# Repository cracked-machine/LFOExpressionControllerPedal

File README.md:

# LFOExpressionControllerPedal
This pedal replaces the traditional treadle/rocker expression pedal as an input into other guitar effects pedals.
Traditional expression pedals allow the player to control a variable resistance via an analog potentiometer in the expression pedal. This pedal creates an LFO signal that sweeps a digital potentiometer. 

The DSP is provided by an ATMEGA328P MCU, which transmits the binary encoded waveform data to a MCP41050 digital potentiometer via SPI. Eight waveforms are available: Sine, Square, RampUp, RampDown, Triangle, 8Step, 4Step and Pulse.
These waveforms can be selected via a single SPDT switch. LEDs indicate the selected waveform. A separate analog pot adjusts the frequency speed.

Documentation:

<ul>
  <li><a href="Hardware/SMT/documentation/LFOControllerPedal_SMT.xml">BOM</a></li>
  <li><a href="Hardware/SMT/documentation/LFOExpController_SMT.pdf">Schematic</a></li>
  <li><a href="Hardware/SMT/documentation/LFOExpController_SMT-TOPbrd.svg">Board Layout (TOP)</a></li>
  <li><a href="Hardware/SMT/documentation/LFOExpController_SMT-BOTTOMbrd.svg">Board Layout (BOTTOM)</a></li>
</ul>

<a href="https://github.com/cracked-machine/LFOExpressionControllerPedal">Github</a>|
<a href="https://cracked-machine.github.io/LFOExpressionControllerPedal/">Pages</a>

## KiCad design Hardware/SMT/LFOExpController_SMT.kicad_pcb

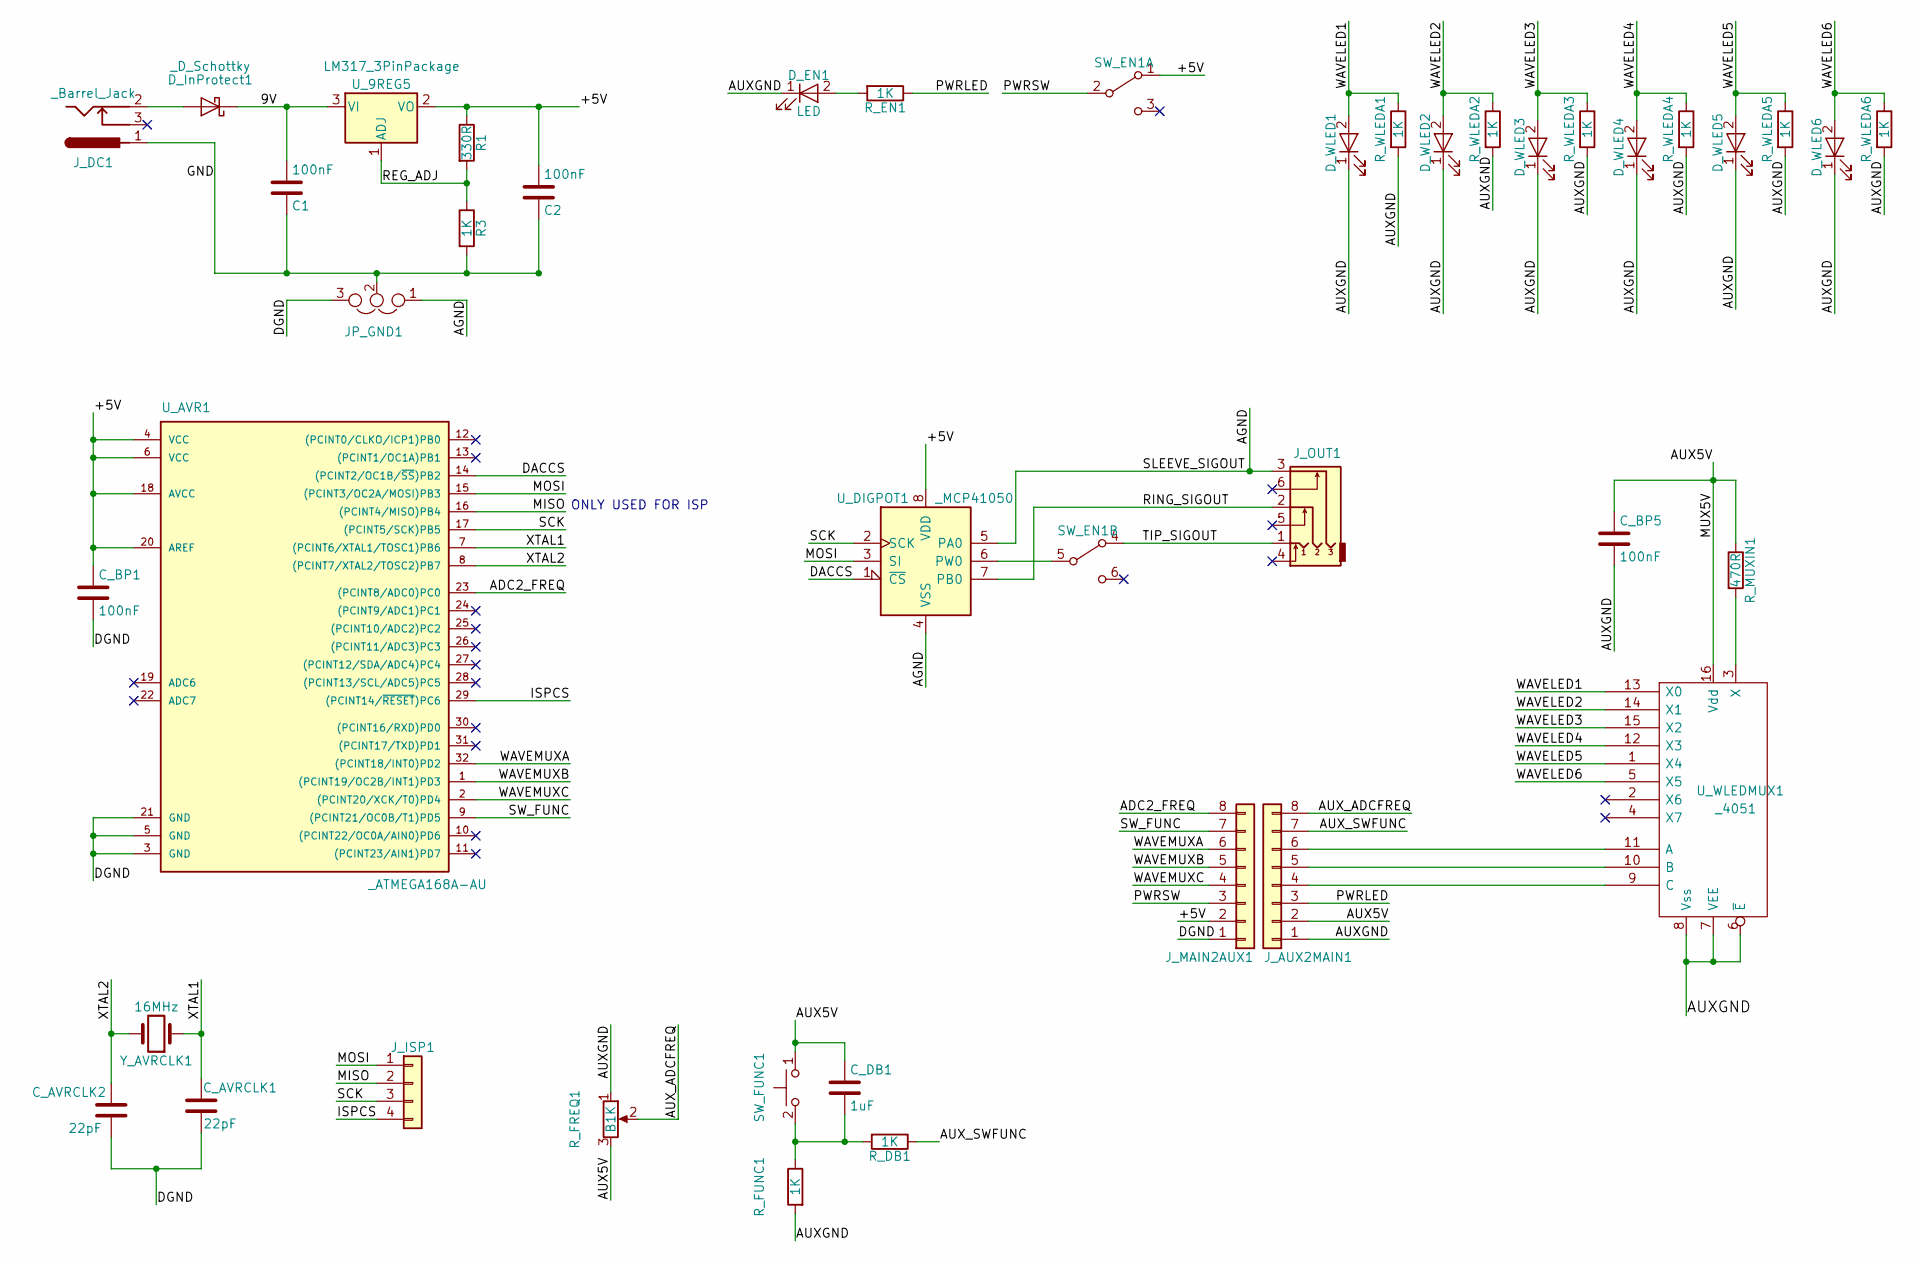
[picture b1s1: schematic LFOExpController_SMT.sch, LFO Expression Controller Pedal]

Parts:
C1, C2: 100nF; C_0805_HandSoldering
C_AVRCLK1, C_AVRCLK2: 22pF; C_0805_HandSoldering
C_BP1, C_BP5: 100nF; C_0805_HandSoldering
C_DB1: 1uF; C_0805_HandSoldering
D_EN1: LED; LED_0805_HandSoldering
D_InProtect1: _D_Schottky; D_SOD-123
D_WLED1, D_WLED2, D_WLED3, D_WLED4, D_WLED5, D_WLED6: LED; LED_0805_HandSoldering
JP_GND1: Jumper_NC_Dual; NetTie-II_SMD_GraphicallyConnected
J_AUX2MAIN1: _Conn_01x08; Pin_Header_Straight_1x08_Pitch2.54mm
J_DC1: _Barrel_Jack; BARREL_JACK
J_ISP1: Conn_01x04; Pin_Header_Straight_1x04_Pitch2.54mm
J_MAIN2AUX1: Conn_01x08; Pin_Header_Straight_1x08_Pitch2.54mm
J_OUT1: Audio-Jack-3_3Switches; TRS635mmJack
R1: 330R; R_0805_HandSoldering
R3: 1K; R_0805_HandSoldering
R_DB1: 1K; R_0805_HandSoldering
R_EN1: 1K; R_0805_HandSoldering
R_FREQ1: B1K; Potentiometer_Bourns_PTV09A-1_Horizontal
R_FUNC1: 1K; R_0805_HandSoldering
R_MUXIN1: 470R; R_0805_HandSoldering
R_WLEDA1, R_WLEDA2, R_WLEDA3, R_WLEDA4, R_WLEDA5, R_WLEDA6: 1K; R_0805_HandSoldering
SW_EN1: SW_DPDT_x2; DPDT_FOOT_ONON_ALPHA_W13MM_D12MM_P5.08MM
SW_FUNC1: SW_Push; SW_PUSH_6mm_h5mm
U_9REG5: LM317_3PinPackage; SOT-223-3_TabPin2
U_AVR1: _ATMEGA168A-AU; TQFP-32_7x7mm_Pitch0.8mm
U_DIGPOT1: _MCP41050; SOIC-8_3.9x4.9mm_Pitch1.27mm
U_WLEDMUX1: _4051; SOIC-16_3.9x9.9mm_Pitch1.27mm
Y_AVRCLK1: 16MHz; Crystal_HC49-4H_Vertical

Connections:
/9V: C1.2, D_InProtect1.1 (K), U_9REG5.3 (VI)
/+5V: C2.2, C_BP1.1, J_MAIN2AUX1.2, R1.1, SW_EN1.1 (A), U_9REG5.2 (VO), U_AVR1.4 (VCC), U_AVR1.6 (VCC), U_AVR1.18 (AVCC), U_AVR1.20 (AREF), U_DIGPOT1.8 (VDD)
/ADC2_FREQ: J_MAIN2AUX1.8, U_AVR1.23 ((PCINT8/ADC0)PC0)
/AGND: JP_GND1.1, J_OUT1.3, U_DIGPOT1.4 (VSS), U_DIGPOT1.5 (PA0)
/AUX5V: C_BP5.1, C_DB1.1, J_AUX2MAIN1.2, R_FREQ1.3, R_MUXIN1.1, SW_FUNC1.1, U_WLEDMUX1.16 (Vdd)
/AUXGND: C_BP5.2, D_EN1.1 (K), D_WLED1.1 (K), D_WLED2.1 (K), D_WLED3.1 (K), D_WLED4.1 (K), D_WLED5.1 (K), D_WLED6.1 (K), J_AUX2MAIN1.1, R_FREQ1.1, R_FUNC1.2, R_WLEDA1.2, R_WLEDA2.2, R_WLEDA3.2, R_WLEDA4.2, R_WLEDA5.2, R_WLEDA6.2, U_WLEDMUX1.6 (~E), U_WLEDMUX1.7 (VEE), U_WLEDMUX1.8 (Vss)
/AUX_ADCFREQ: J_AUX2MAIN1.8, R_FREQ1.2
/AUX_SWFUNC: J_AUX2MAIN1.7, R_DB1.1
/DACCS: U_AVR1.14 ((PCINT2/OC1B/~SS~)PB2), U_DIGPOT1.1 (~CS)
/DGND: C_AVRCLK1.1, C_AVRCLK2.1, C_BP1.2, JP_GND1.3, J_MAIN2AUX1.1, U_AVR1.3 (GND), U_AVR1.5 (GND), U_AVR1.21 (GND)
/GND: C1.1, C2.1, JP_GND1.2, J_DC1.1, R3.2
/ISPCS: J_ISP1.4, U_AVR1.29 ((PCINT14/~RESET~)PC6)
/MISO: J_ISP1.2, U_AVR1.16 ((PCINT4/MISO)PB4)
/MOSI: J_ISP1.1, U_AVR1.15 ((PCINT3/OC2A/MOSI)PB3), U_DIGPOT1.3 (SI)
/PWRLED: J_AUX2MAIN1.3, R_EN1.1
/PWRSW: J_MAIN2AUX1.3, SW_EN1.2 (B)
/REG_ADJ: R1.2, R3.1, U_9REG5.1 (ADJ)
/RING_SIGOUT: J_OUT1.2, U_DIGPOT1.7 (PB0)
/SCK: J_ISP1.3, U_AVR1.17 ((PCINT5/SCK)PB5), U_DIGPOT1.2 (SCK)
/SW_FUNC: J_MAIN2AUX1.7, U_AVR1.9 ((PCINT21/OC0B/T1)PD5)
/TIP_SIGOUT: J_OUT1.1, SW_EN1.4 (A)
/WAVELED1: D_WLED1.2 (A), R_WLEDA1.1, U_WLEDMUX1.13 (X0)
/WAVELED2: D_WLED2.2 (A), R_WLEDA2.1, U_WLEDMUX1.14 (X1)
/WAVELED3: D_WLED3.2 (A), R_WLEDA3.1, U_WLEDMUX1.15 (X2)
/WAVELED4: D_WLED4.2 (A), R_WLEDA4.1, U_WLEDMUX1.12 (X3)
/WAVELED5: D_WLED5.2 (A), R_WLEDA5.1, U_WLEDMUX1.1 (X4)
/WAVELED6: D_WLED6.2 (A), R_WLEDA6.1, U_WLEDMUX1.5 (X5)
/WAVEMUXA: J_MAIN2AUX1.6, U_AVR1.32 ((PCINT18/INT0)PD2)
/WAVEMUXB: J_MAIN2AUX1.5, U_AVR1.1 ((PCINT19/OC2B/INT1)PD3)
/WAVEMUXC: J_MAIN2AUX1.4, U_AVR1.2 ((PCINT20/XCK/T0)PD4)
/XTAL1: C_AVRCLK1.2, U_AVR1.7 ((PCINT6/XTAL1/TOSC1)PB6), Y_AVRCLK1.1
/XTAL2: C_AVRCLK2.2, U_AVR1.8 ((PCINT7/XTAL2/TOSC2)PB7), Y_AVRCLK1.2
unnamed: C_DB1.2, R_DB1.2, R_FUNC1.1, SW_FUNC1.2
unnamed: D_EN1.2 (A), R_EN1.2
unnamed: D_InProtect1.2 (A), J_DC1.2
unnamed: J_AUX2MAIN1.4, U_WLEDMUX1.9 (C)
unnamed: J_AUX2MAIN1.5, U_WLEDMUX1.10 (B)
unnamed: J_AUX2MAIN1.6, U_WLEDMUX1.11 (A)
unnamed: R_MUXIN1.2, U_WLEDMUX1.3 (X)
unnamed: SW_EN1.5 (B), U_DIGPOT1.6 (PW0)

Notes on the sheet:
ONLY USED FOR ISP

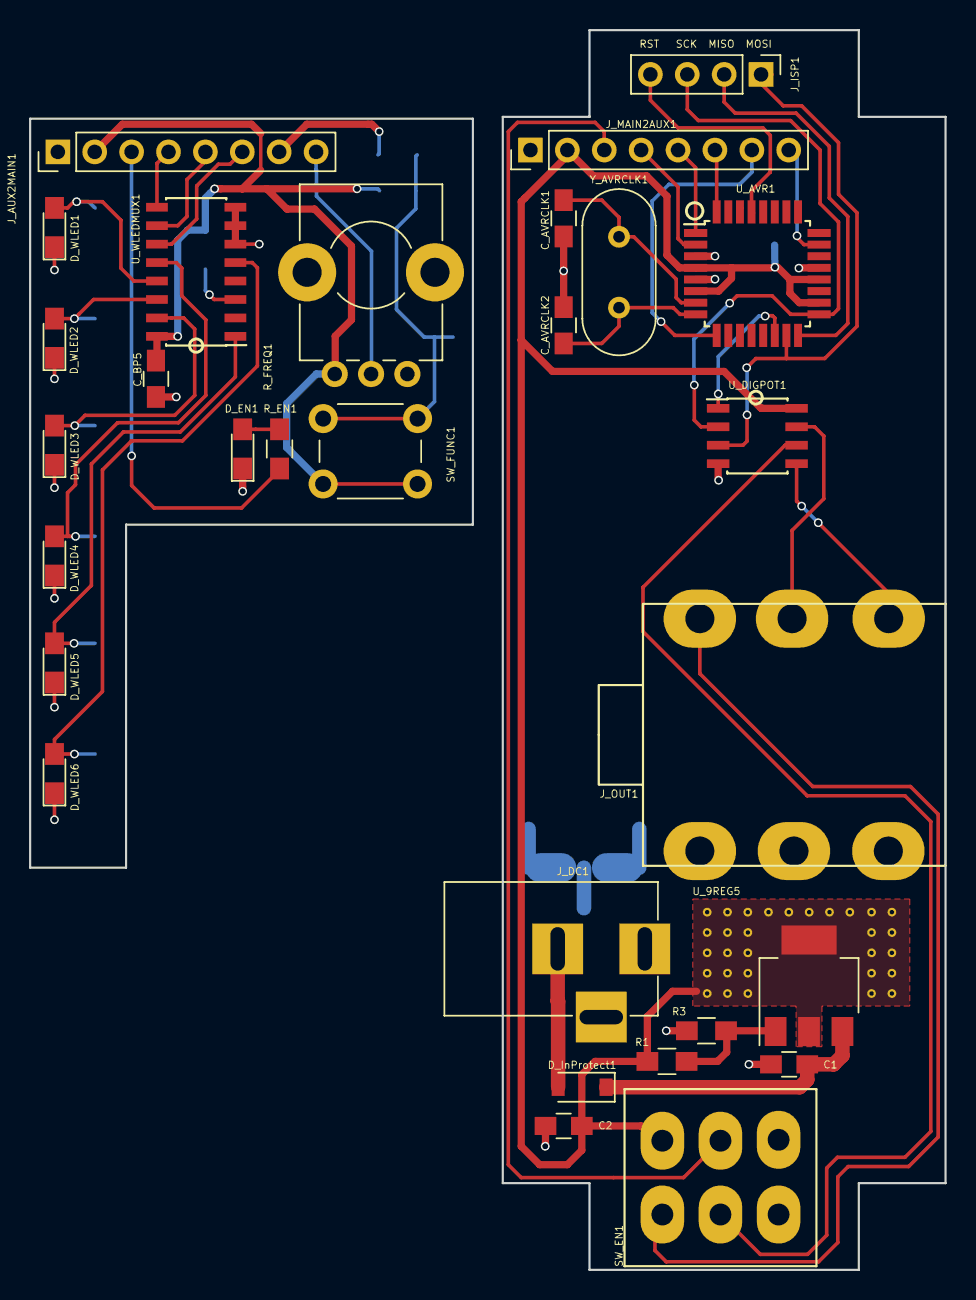
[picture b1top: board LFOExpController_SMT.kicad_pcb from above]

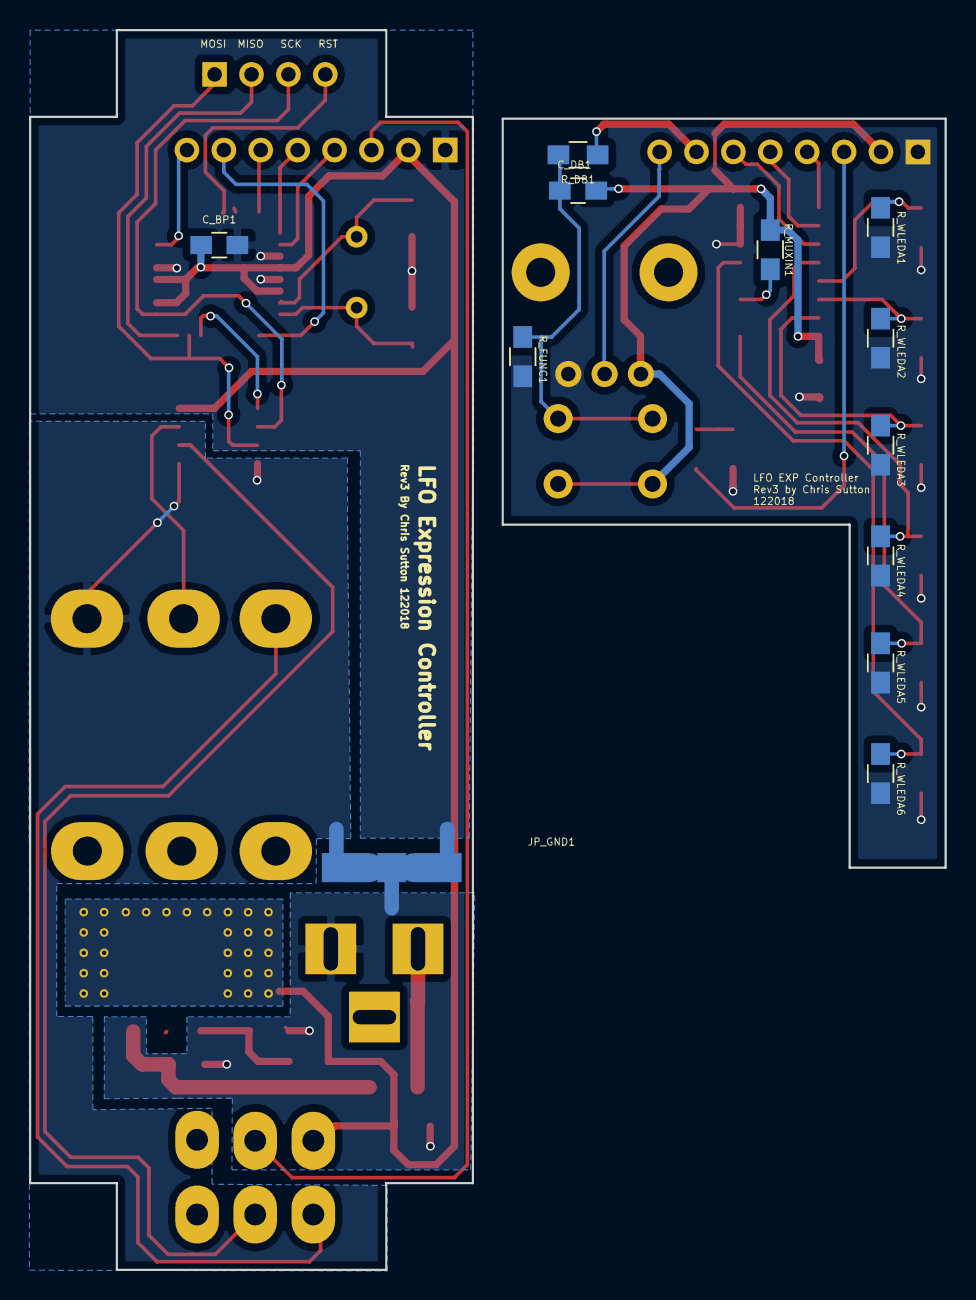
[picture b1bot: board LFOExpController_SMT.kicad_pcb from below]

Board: 2 copper layers, 63.0 x 85.3 mm, 41 parts (12 on the bottom side), 40 nets.

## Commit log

2018-03-10 correction
2018-03-10 Completed Board Layout
2018-03-11 Generated GERBERS
2018-03-15 Set theme jekyll-theme-midnight
2018-03-24 Revision3 update
    - Added ground to Jack sleeve pin
    - Corrected SW_FUNC circuit
    - Removed R_WLEDB LEDS
    - Modified firmware from eight wavepatterns to six, to allign with Hardware (Sine, Triangle, RampUp, Step4, Square, Pulse)
    - Created R3 documentation
    - Created new GERBERS
2018-03-24 save update
2018-03-31 Set theme jekyll-theme-slate
2018-06-02 board layout update
    - rotated freq pot 180 and moved up 5mm
    - narrowed led strip on daughter board
